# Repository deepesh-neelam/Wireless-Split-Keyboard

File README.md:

# Wireless Split Mechanical Keyboard

A custom wireless split mechanical keyboard designed from scratch as part of the Hack Club Stasis program.

## Features
- Wireless via Bluetooth (nRF52840)
- Split design with 21 keys per half
- Kailh Choc V1 hotswap sockets
- Column stagger layout
- Battery powered with voltage sensing
- ZMK firmware compatible

## Hardware
- MCU: Seeed XIAO nRF52840
- Switches: Kailh Choc V1 (hotswap)
- Diodes: 1N5819 SOD-123
- PCB designed in KiCad 9.0

## Libraries Used
- marbastlib (switch footprints)
- Panelization.pretty (mousebites)

## Firmware
This keyboard uses ZMK firmware. See the ZMK documentation for setup instructions.

## Status
PCB design complete — pending manufacturing and assembly.

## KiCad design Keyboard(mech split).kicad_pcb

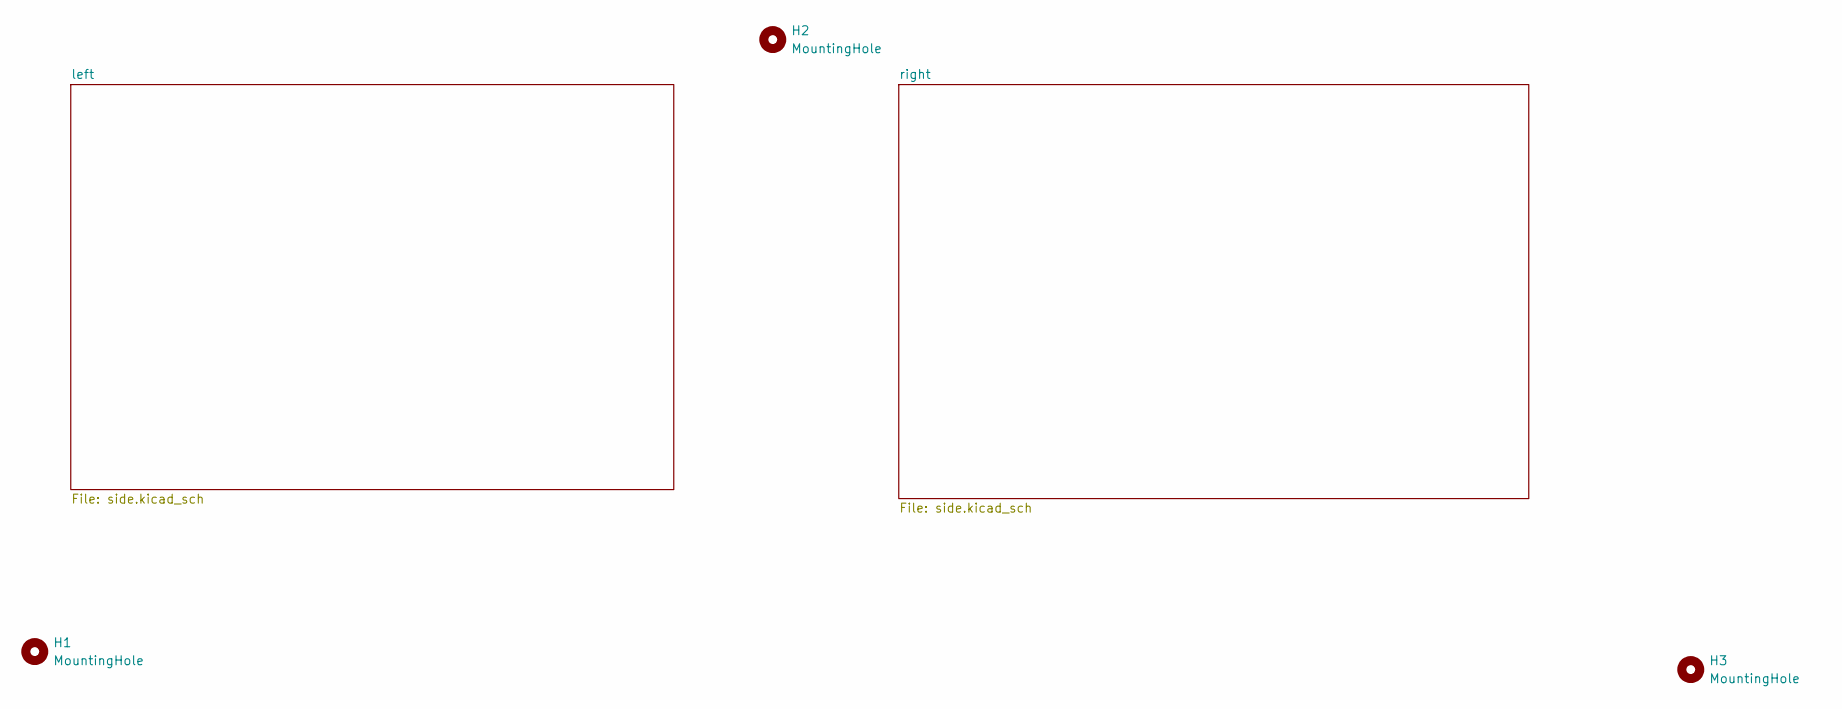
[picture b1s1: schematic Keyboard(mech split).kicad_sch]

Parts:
H1, H2, H3: MountingHole; mouse-bite-5mm-slot

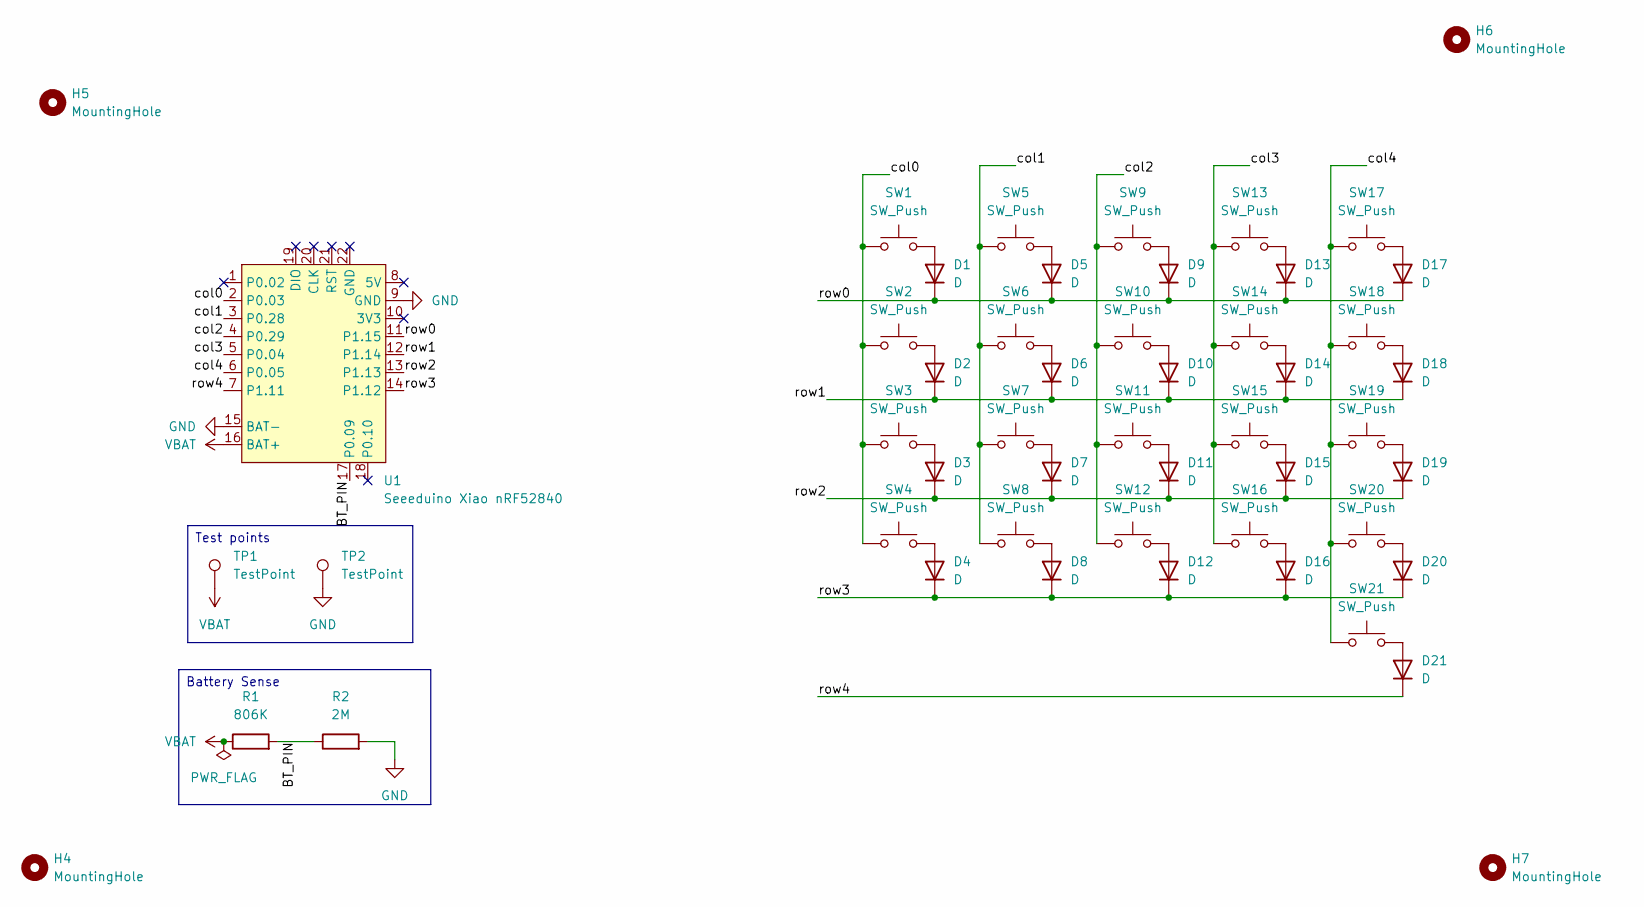
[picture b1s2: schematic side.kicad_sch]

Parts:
D1, D2, D3, D4, D5, D6, D7, D8, D9, D10, D11, D12, D13, D14, D15, D16, D17, D18, D19, D20, D21: D; D_SOD-123
H4, H5, H6, H7: MountingHole; MountingHole_2.2mm_M2
R1: 806K; R_0805_2012Metric
R2: 2M; R_0805_2012Metric
SW1, SW2, SW3, SW4, SW5, SW6, SW7, SW8, SW9, SW10, SW11, SW12, SW13, SW14, SW15, SW16, SW17, SW18, SW19, SW20, SW21: SW_Push; SW_choc_v1_HS_CPG135001S30_1.25u
TP1, TP2: TestPoint; TestPoint_Pad_D2.0mm
U1: Seeeduino Xiao nRF52840; modified-XIAO-nRF52840-SMD (3)

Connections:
/left/BT_PIN: R1.2, R2.1, U1.17 (P0.09)
/left/col0: SW1.1, SW2.1, SW3.1, SW4.1, U1.2 (P0.03)
/left/col1: SW5.1, SW6.1, SW7.1, SW8.1, U1.3 (P0.28)
/left/col2: SW9.1, SW10.1, SW11.1, SW12.1, U1.4 (P0.29)
/left/col3: SW13.1, SW14.1, SW15.1, SW16.1, U1.5 (P0.04)
/left/col4: SW17.1, SW18.1, SW19.1, SW20.1, SW21.1, U1.6 (P0.05)
/left/row0: D1.1 (K), D5.1 (K), D9.1 (K), D13.1 (K), D17.1 (K), U1.11 (P1.15)
/left/row1: D2.1 (K), D6.1 (K), D10.1 (K), D14.1 (K), D18.1 (K), U1.12 (P1.14)
/left/row2: D3.1 (K), D7.1 (K), D11.1 (K), D15.1 (K), D19.1 (K), U1.13 (P1.13)
/left/row3: D4.1 (K), D8.1 (K), D12.1 (K), D16.1 (K), D20.1 (K), U1.14 (P1.12)
/left/row4: D21.1 (K), U1.7 (P1.11)
GND: R2.2, TP2.1, U1.9 (GND), U1.15 (BAT-); also elsewhere on the board
unnamed: D1.2 (A), SW1.2
unnamed: D2.2 (A), SW2.2
unnamed: D3.2 (A), SW3.2
unnamed: D4.2 (A), SW4.2
unnamed: D5.2 (A), SW5.2
unnamed: D6.2 (A), SW6.2
unnamed: D7.2 (A), SW7.2
unnamed: D8.2 (A), SW8.2
unnamed: D9.2 (A), SW9.2
unnamed: D10.2 (A), SW10.2
unnamed: D11.2 (A), SW11.2
unnamed: D12.2 (A), SW12.2
unnamed: D13.2 (A), SW13.2
unnamed: D14.2 (A), SW14.2
unnamed: D15.2 (A), SW15.2
unnamed: D16.2 (A), SW16.2
unnamed: D17.2 (A), SW17.2
unnamed: D18.2 (A), SW18.2
unnamed: D19.2 (A), SW19.2
unnamed: D20.2 (A), SW20.2
unnamed: D21.2 (A), SW21.2
VBAT: R1.1, TP1.1, U1.16 (BAT+); also elsewhere on the board

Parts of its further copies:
D22, D23, D24, D25, D26, D27, D28, D29, D30, D31, D32, D33, D34, D35, D36, D37, D38, D39, D40, D41, D42: D; D_SOD-123
H8, H9, H10, H11: MountingHole; MountingHole_2.2mm_M2
R3: 806K; R_0805_2012Metric
R4: 2M; R_0805_2012Metric
SW22, SW23, SW24, SW25, SW26, SW27, SW28, SW29, SW30, SW31, SW32, SW33, SW34, SW35, SW36, SW37, SW38, SW39, SW40, SW41, SW42: SW_Push; SW_choc_v1_HS_CPG135001S30_1.25u
TP3, TP4: TestPoint; TestPoint_Pad_D2.0mm
U2: Seeeduino Xiao nRF52840; modified-XIAO-nRF52840-SMD (3)

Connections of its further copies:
/right/BT_PIN: R3.2, R4.1, U2.17 (P0.09)
/right/col0: SW22.1, SW23.1, SW24.1, SW25.1, U2.2 (P0.03)
/right/col1: SW26.1, SW27.1, SW28.1, SW29.1, U2.3 (P0.28)
/right/col2: SW30.1, SW31.1, SW32.1, SW33.1, U2.4 (P0.29)
/right/col3: SW34.1, SW35.1, SW36.1, SW37.1, U2.5 (P0.04)
/right/col4: SW38.1, SW39.1, SW40.1, SW41.1, SW42.1, U2.6 (P0.05)
/right/row0: D22.1 (K), D26.1 (K), D30.1 (K), D34.1 (K), D38.1 (K), U2.11 (P1.15)
/right/row1: D23.1 (K), D27.1 (K), D31.1 (K), D35.1 (K), D39.1 (K), U2.12 (P1.14)
/right/row2: D24.1 (K), D28.1 (K), D32.1 (K), D36.1 (K), D40.1 (K), U2.13 (P1.13)
/right/row3: D25.1 (K), D29.1 (K), D33.1 (K), D37.1 (K), D41.1 (K), U2.14 (P1.12)
/right/row4: D42.1 (K), U2.7 (P1.11)
GND: R4.2, TP4.1, U2.9 (GND), U2.15 (BAT-); also elsewhere on the board
unnamed: D22.2 (A), SW22.2
unnamed: D23.2 (A), SW23.2
unnamed: D24.2 (A), SW24.2
unnamed: D25.2 (A), SW25.2
unnamed: D26.2 (A), SW26.2
unnamed: D27.2 (A), SW27.2
unnamed: D28.2 (A), SW28.2
unnamed: D29.2 (A), SW29.2
unnamed: D30.2 (A), SW30.2
unnamed: D31.2 (A), SW31.2
unnamed: D32.2 (A), SW32.2
unnamed: D33.2 (A), SW33.2
unnamed: D34.2 (A), SW34.2
unnamed: D35.2 (A), SW35.2
unnamed: D36.2 (A), SW36.2
unnamed: D37.2 (A), SW37.2
unnamed: D38.2 (A), SW38.2
unnamed: D39.2 (A), SW39.2
unnamed: D40.2 (A), SW40.2
unnamed: D41.2 (A), SW41.2
unnamed: D42.2 (A), SW42.2
VBAT: R3.1, TP3.1, U2.16 (BAT+); also elsewhere on the board

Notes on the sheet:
Test points
Battery Sense

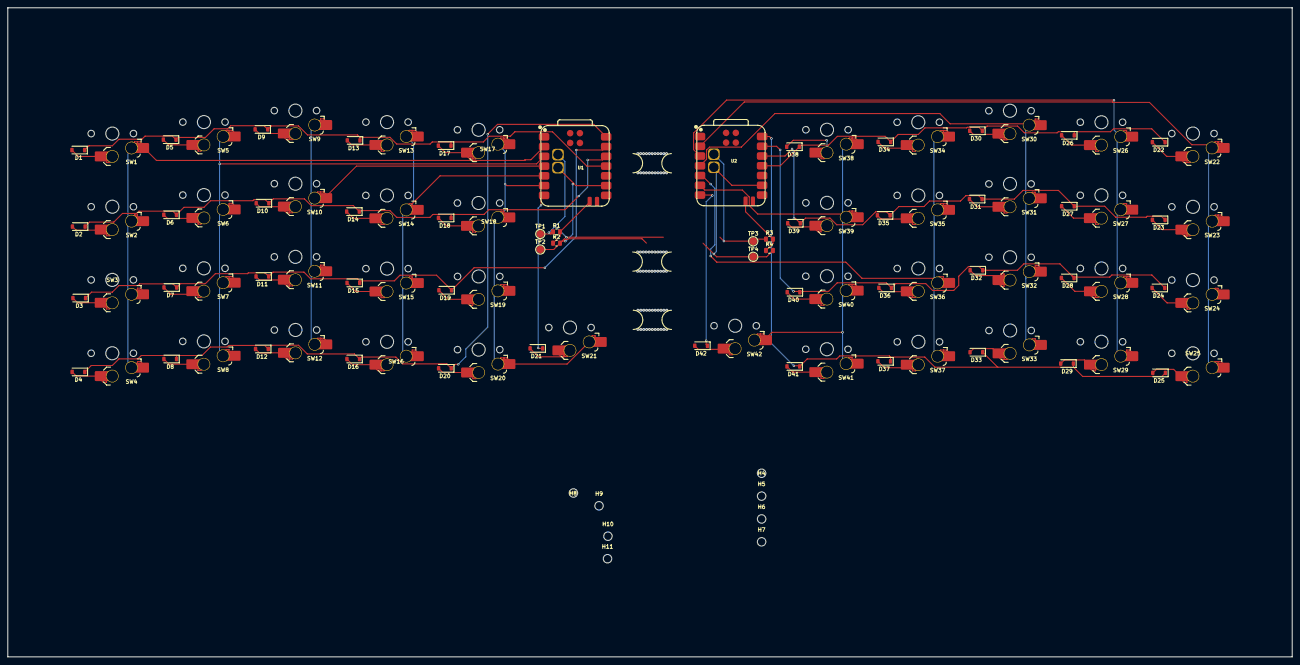
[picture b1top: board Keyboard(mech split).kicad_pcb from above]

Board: 2 copper layers, 334.4 x 169.0 mm, 105 parts (0 on the bottom side), 66 nets.

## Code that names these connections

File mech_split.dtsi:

#include <dt-bindings/zmk/matrix_transform.h>

/ {
    chosen {
        zmk,kscan = &kscan0;
        zmk,matrix_transform = &default_transform;
    };

    default_transform: keymap_transform_0 {
        compatible = "zmk,matrix-transform";
        columns = <5>;
        rows = <5>;
        map = 
            RC(0,0) RC(0,1) RC(0,2) RC(0,3) RC(0,4)
            RC(1,0) RC(1,1) RC(1,2) RC(1,3) RC(1,4)
            RC(2,0) RC(2,1) RC(2,2) RC(2,3) RC(2,4)
            RC(3,0) RC(3,1) RC(3,2) RC(3,3) RC(3,4)
                                            RC(4,4)
        >;
    };

    kscan0: kscan {
        compatible = "zmk,kscan-gpio-matrix";
        label = "KSCAN";
        diode-direction = "col2row";

        col-gpios
            = <&gpio0 3  GPIO_ACTIVE_HIGH>   /* col0 P0.03 */
            , <&gpio0 28 GPIO_ACTIVE_HIGH>   /* col1 P0.28 */
            , <&gpio0 29 GPIO_ACTIVE_HIGH>   /* col2 P0.29 */
            , <&gpio0 4  GPIO_ACTIVE_HIGH>   /* col3 P0.04 */
            , <&gpio0 5  GPIO_ACTIVE_HIGH>   /* col4 P0.05 */
            ;

        row-gpios
            = <&gpio1 15 (GPIO_ACTIVE_HIGH | GPIO_PULL_DOWN)>  /* row0 P1.15 */
            , <&gpio1 14 (GPIO_ACTIVE_HIGH | GPIO_PULL_DOWN)>  /* row1 P1.14 */
            , <&gpio1 13 (GPIO_ACTIVE_HIGH | GPIO_PULL_DOWN)>  /* row2 P1.13 */
            , <&gpio1 12 (GPIO_ACTIVE_HIGH | GPIO_PULL_DOWN)>  /* row3 P1.12 */
            , <&gpio1 11 (GPIO_ACTIVE_HIGH | GPIO_PULL_DOWN)>  /* row4 P1.11 */
            ;
    };
};
